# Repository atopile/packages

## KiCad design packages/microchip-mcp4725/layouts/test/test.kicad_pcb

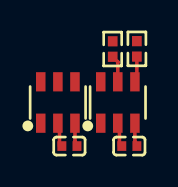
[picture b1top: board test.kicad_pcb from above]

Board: 2 copper layers, 6 parts (0 on the bottom side), 5 nets.

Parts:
C1, C2: 1F; C0402
R1, R2: 10000Ω; R0402
U1, U2: SOT-23-6_L2.9-W1.6-P0.95-LS2.8-BL

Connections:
SCL: R1.1, U1.5, U2.5
SDA: R2.1, U1.4, U2.4
hv: C1.1, C2.1, U1.3, U2.3, U2.6
i2c-hv: R1.2, R2.2
lv: C1.2, C2.2, U1.2, U1.6, U2.2

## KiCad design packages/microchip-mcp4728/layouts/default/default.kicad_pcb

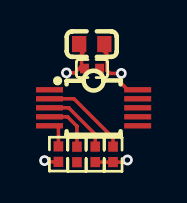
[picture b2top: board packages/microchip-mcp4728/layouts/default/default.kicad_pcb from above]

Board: 2 copper layers, 7 parts (0 on the bottom side), 6 nets.

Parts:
C1: 1±10.0%F; C0402
C2: {8.999..1.1}F; C0603
R1, R2, R3: 10000±1.0%Ω; R0402
R4: 100000±1.0%Ω; R0402
U1: MSOP-10_L3.0-W3.0-P0.50-LS5.0-TL

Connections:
RDY_nBSY: R4.1, U1.5
SCL: R1.1, U1.2
SDA: R2.1, U1.3
hv: C1.1, C2.1, R1.2, R2.2, R4.2, U1.1
lv: C1.2, C2.2, R3.2, U1.10
nLDAC: R3.1, U1.4

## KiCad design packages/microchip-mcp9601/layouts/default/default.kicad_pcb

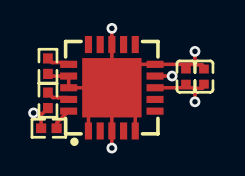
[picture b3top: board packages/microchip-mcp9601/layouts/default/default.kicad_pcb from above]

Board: 2 copper layers, 6 parts (0 on the bottom side), 5 nets.

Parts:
C1, C2: 1F; C0402
R1: 0Ω; R0402
R2, R3: 10000Ω; R0402
U1: TQFN-20_L5.0-W5.0-P0.65-BL-EP3.3

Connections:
ADDR: R1.1, U1.16
SCL: R2.1, U1.19
SDA: R3.1, U1.20
hv: C1.1, C2.1, R2.2, R3.2, U1.8
lv: C1.2, C2.2, R1.2, U1.1, U1.3, U1.5, U1.10, U1.13, U1.17, U1.18, U1.21
